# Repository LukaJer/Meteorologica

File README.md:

# Meteorologica

## A ultra-low-power, flexible Environment Monitioring Platform  

### Hardware Desctiption:  
- uC: STM32G071
- LoRa Module: RFM95
- power management: BQ25060 (4.4V - 10.2V input)
- I2C 
- 5 GPIOs: (PA0 (int0), PA8, PA15, PB3, PB5)
- JST ZH 1.5mm connectors
- 1.27mm header for for programming and debugging (SWD+UART)
#### Detailed Description  
It's centered around a STM32G071 microcontroller and uses LoRa for efficient and longish range communication. Currently it sends to a custom Gateway which forwards the data to a MQTT server but the code can be easily adapted to use another LoRa infrastructure like The Things Network. The LoRa Module is a RFM95.  
A 18650 cell (other Li Ion batterys can be used too) is used for power  which can be charged from a powersource (4.4V - 10.2V) or via USB-C. The charging is done by a TI BQ25060 which offers semi-MPPT functionality. The uC can read the solar and battery voltage.  
There are 5 GPIOs available (PA0 (int0), PA8, PA15, PB3, PB5) and a I2C bus. All GPIOs have footprints for pull-up/-down resistors or capacitors and 3V3 and GND connections next to them. JST ZH 1.5mm connectors are used and a 1.27mm header is present for programming and debugging (SWD+UART). Each sensor can be either powered directly from 3V3 or a toggleable 3V3 bus . NOTE: the toggleable bus is implemented in Hardware but untested and has currently software support.

### Software Description:
The project is written in Arduino.  
Each Station has it's own name so multiple can be used on a single Gateway. 
The station wakes up in specified Intervalls (2min) and checks if any of the sensor values have changed, if so it sends the data as a JSON to the Gatway. The data is send every 10th wakeup no matter the values as a heartbeat. 
Currently
- Bosch BME280
- Sensiron SHT31
- Lacrosse TX23
- MaXIM DS18B20
- generic simple rain sensor
are implemented an can be enabled by uncommenting code.

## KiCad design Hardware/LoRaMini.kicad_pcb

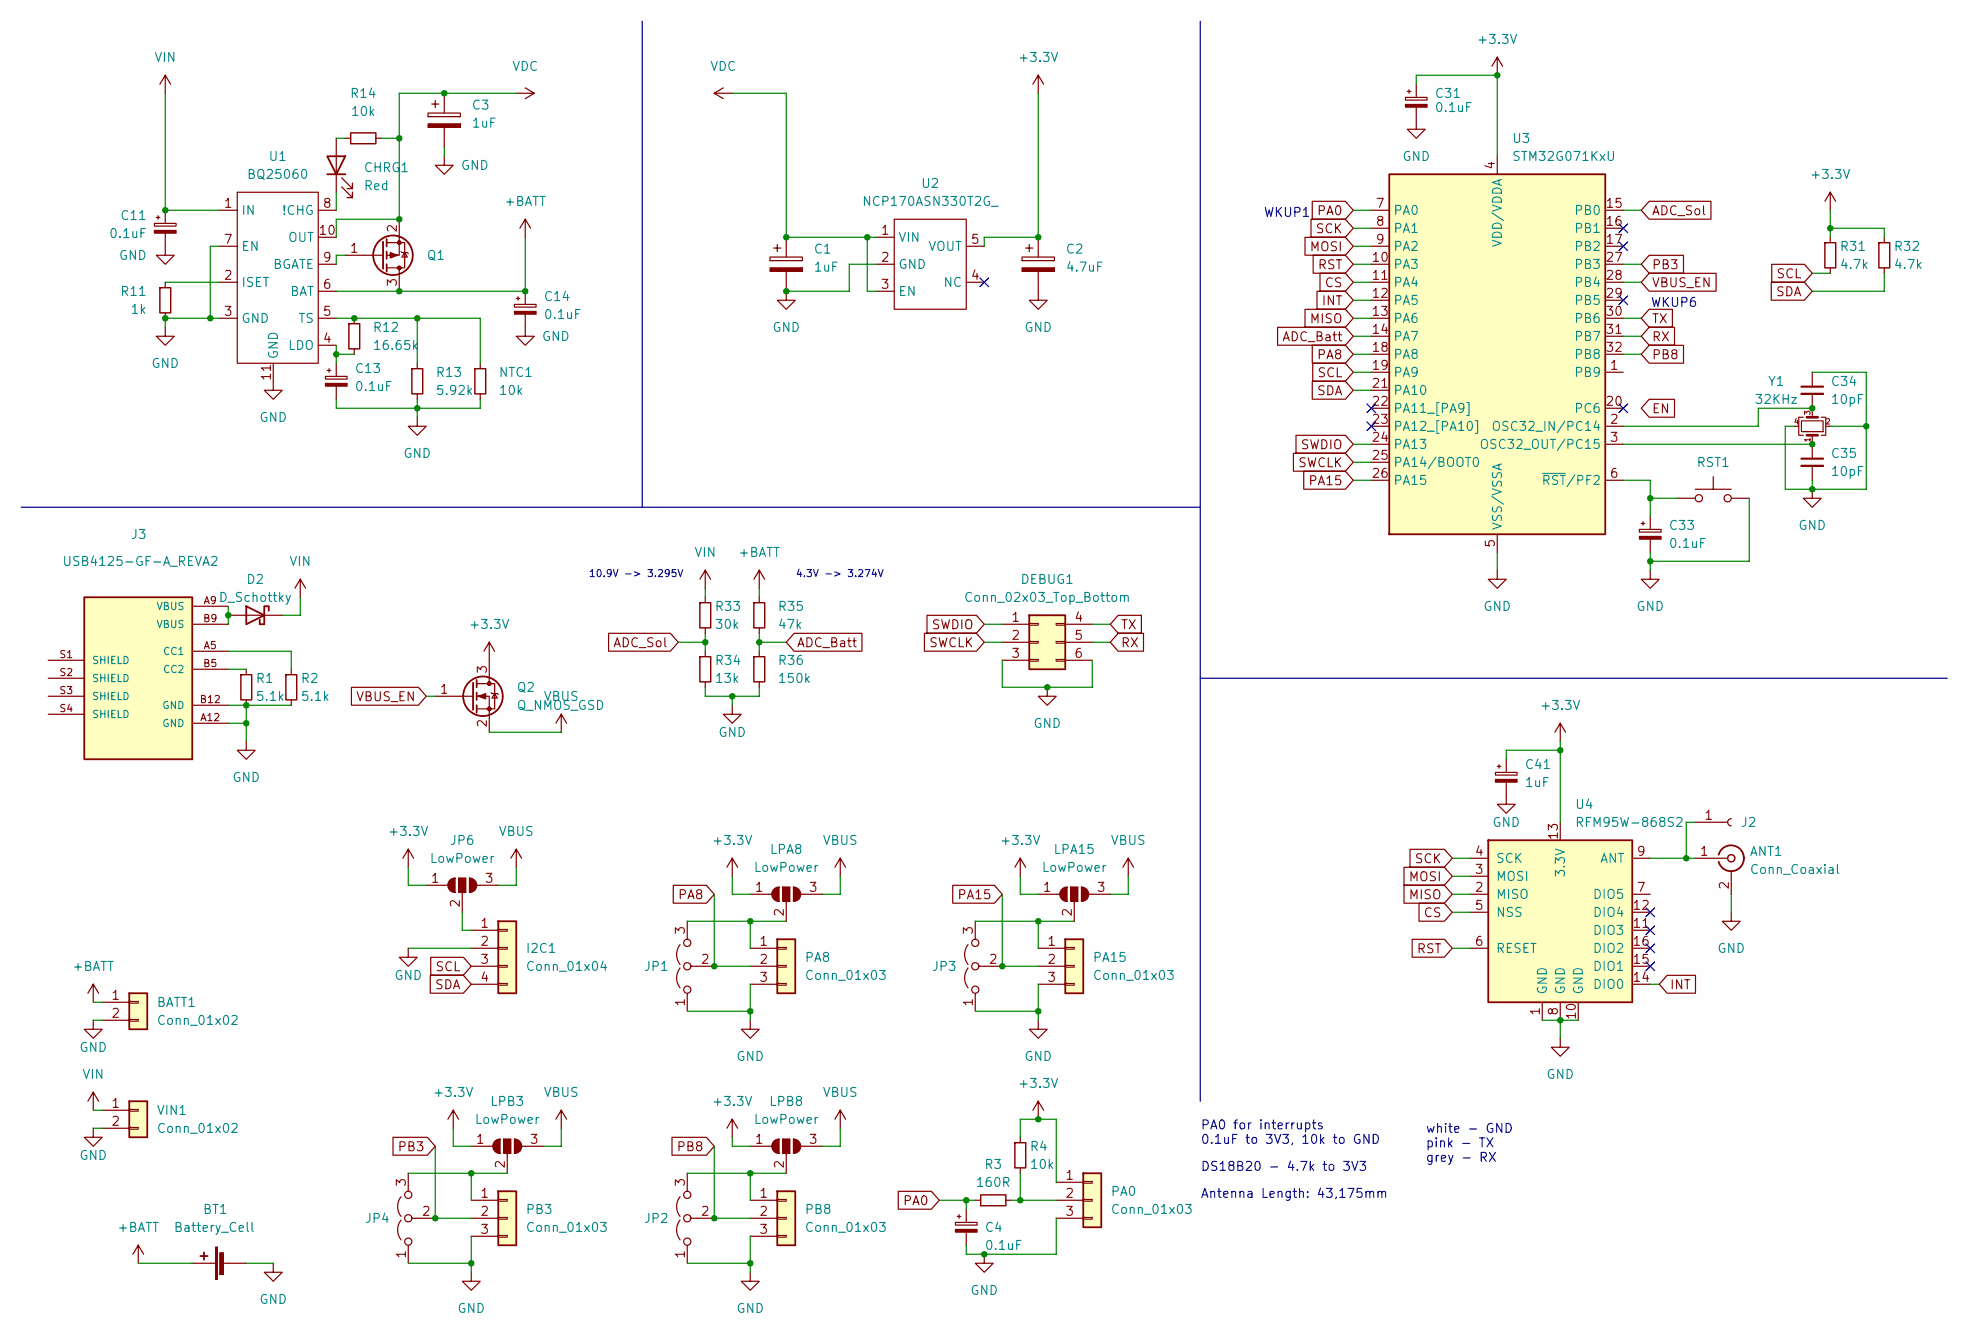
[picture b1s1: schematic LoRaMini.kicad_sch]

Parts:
ANT1: Conn_Coaxial; U.FL_Hirose_U.FL-R-SMT-1_Vertical
BATT1: Conn_01x02; JST_S2B-ZR-SM4A-TF(LF)(SN)
BT1: Battery_Cell; BatteryHolder_1x18650
C1, C3, C41: 1uF; C_1206_3216Metric
C2: 4.7uF; C_1206_3216Metric
C4, C13, C31, C33: 0.1uF; C_0805_2012Metric
C11, C14: 0.1uF; C_1206_3216Metric
C34, C35: 10pF; C_0805_2012Metric
CHRG1: Red; LED_1206_3216Metric
D2: D_Schottky; Nexperia_CFP3_SOD-123W
DEBUG1: Conn_02x03_Top_Bottom; PinHeader_2x03_P1.27mm_Vertical_SMD_My
I2C1: Conn_01x04; JST_S4B-ZR-SM4A-TF(LF)(SN)
J2: Conn_01x01_Female; Pin_D1.0mm_L10.0mm
J3: USB4125-GF-A_REVA2; GCT_USB4125-GF-A_REVA2; PARTREV Rev A2
JP1, JP2, JP3, JP4: Jumper_3_Open; Jumper_3_0805
JP6: LowPower; SolderJumper-3_P1.3mm_Open_Pad1.0x1.5mm
LPA8, LPA15: LowPower; SolderJumper-3_P1.3mm_Open_Pad1.0x1.5mm
LPB3, LPB8: LowPower; SolderJumper-3_P1.3mm_Open_Pad1.0x1.5mm
NTC1: 10k; R_0805_2012Metric
PA0, PA8, PA15: Conn_01x03; JST_S3B-ZR-SM4A-TF
PB3, PB8: Conn_01x03; JST_S3B-ZR-SM4A-TF
Q1: Q_PMOS_GSD; SOT-23
Q2: Q_NMOS_GSD; SOT-23
R1, R2: 5.1k; R_0805_2012Metric
R3: 160R; R_0805_2012Metric
R4, R14: 10k; R_0805_2012Metric
R11: 1k; R_0805_2012Metric
R12: 16.65k; R_0805_2012Metric
R13: 5.92k; R_0805_2012Metric
R31, R32: 4.7k; R_0805_2012Metric
R33: 30k; R_0805_2012Metric
R34: 13k; R_0805_2012Metric
R35: 47k; R_0805_2012Metric
R36: 150k; R_0805_2012Metric
RST1: SW_Push; SW_Push_SPST_NO_Alps_SKRK
U1: BQ25060; WSON-10-1EP_2x3mm_P0.5mm_EP0.84x2.4mm
U2: NCP170ASN330T2G_; TSOP-5_1.65x3.05mm_P0.95mm
U3: STM32G071KxU; UFQFPN-32-1EP_5x5mm_P0.5mm_EP3.5x3.5mm
U4: RFM95W-868S2; HOPERF_RFM9XW_SMD
VIN1: Conn_01x02; JST_S2B-ZR-SM4A-TF(LF)(SN)
Y1: 32KHz; Crystal_SMD_2520-4Pin_2.5x2.0mm

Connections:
+3V3: C2.1, C31.1, C41.1, JP6.1 (A), LPA8.1 (A), LPA15.1 (A), LPB3.1 (A), LPB8.1 (A), PA0.1, Q2.3 (D), R4.1, R31.1, R32.1, U2.5 (VOUT), U3.4 (VDD/VDDA), U4.13 (3.3V)
+BATT: BATT1.1, BT1.1 (+), C14.1, Q1.3 (D), R35.1, U1.6 (BAT); also elsewhere on the board
ADC_Batt: R35.2, R36.1, U3.14 (PA7)
ADC_Sol: R33.2, R34.1, U3.15 (PB0)
CS: U3.11 (PA4), U4.5 (NSS)
GND: ANT1.2 (Ext), BATT1.2, BT1.2 (-), C1.2, C2.2, C3.2, C4.2, C11.2, C13.2, C14.2, C31.2, C33.2, C34.1, C35.2, C41.2, DEBUG1.3, DEBUG1.6, I2C1.2, J3.A12 (GND), J3.B12 (GND), JP1.1 (A), JP2.1 (A), JP3.1 (A), JP4.1 (A), NTC1.2, PA0.3, PA8.3, PA15.3, PB3.3, PB8.3, R1.2, R2.2, R11.2, R13.2, R34.2, R36.2, RST1.2, U1.3 (GND), U1.7 (EN), U1.11 (GND), U2.2 (GND), U3.5 (VSS/VSSA), U3.33 (VSS/VSSA), U4.1 (GND), U4.8 (GND), U4.10 (GND), VIN1.2, Y1.2, Y1.4; also elsewhere on the board
INT: U3.12 (PA5), U4.14 (DIO0)
MISO: U3.13 (PA6), U4.2 (MISO)
MOSI: U3.9 (PA2), U4.3 (MOSI)
unnamed 9: ANT1.1 (In), J2.1, U4.9 (ANT); also elsewhere on the board
unnamed: C13.1, R12.2, U1.4 (LDO)
unnamed 11: C33.1, RST1.1, U3.6 (~RST/PF2); also elsewhere on the board
unnamed: C34.2, U3.2 (OSC32_IN/PC14), Y1.3
unnamed: C35.1, U3.3 (OSC32_OUT/PC15), Y1.1
unnamed: CHRG1.1 (K), U1.8 (!CHG)
unnamed: CHRG1.2 (A), R14.1
unnamed: D2.2 (A), J3.A9 (VBUS), J3.B9 (VBUS)
unnamed 17: I2C1.1, JP6.2 (C); also elsewhere on the board
unnamed: J3.A5 (CC1), R2.1
unnamed: J3.B5 (CC2), R1.1
unnamed: JP1.3 (B), LPA8.2 (C), PA8.1
unnamed: JP2.3 (B), LPB8.2 (C), PB8.1
unnamed: JP3.3 (B), LPA15.2 (C), PA15.1
unnamed: JP4.3 (B), LPB3.2 (C), PB3.1
unnamed: NTC1.1, R12.1, R13.1, U1.5 (TS)
unnamed: PA0.2, R3.2, R4.2
unnamed: Q1.1 (G), U1.9 (BGATE)
unnamed: R11.1, U1.2 (ISET)
PA0: C4.1, R3.1, U3.7 (PA0)
PA8: JP1.2 (C), PA8.2, U3.18 (PA8)
PA15: JP3.2 (C), PA15.2, U3.26 (PA15)
PB3: JP4.2 (C), PB3.2, U3.27 (PB3)
PB8: JP2.2 (C), PB8.2, U3.32 (PB8)
RST: U3.10 (PA3), U4.6 (RESET)
RX: DEBUG1.5, U3.31 (PB7)
SCK: U3.8 (PA1), U4.4 (SCK)
SCL: I2C1.3, R31.2, U3.19 (PA9); also elsewhere on the board
SDA: I2C1.4, R32.2, U3.21 (PA10); also elsewhere on the board
SWCLK: DEBUG1.2, U3.25 (PA14/BOOT0)
SWDIO: DEBUG1.1, U3.24 (PA13)
TX: DEBUG1.4, U3.30 (PB6)
VBUS: JP6.3 (B), LPA8.3 (B), LPA15.3 (B), LPB3.3 (B), LPB8.3 (B), Q2.2 (S)
VBUS_EN: Q2.1 (G), U3.28 (PB4)
VDC: C1.1, C3.1, Q1.2 (S), R14.2, U1.10 (OUT), U2.1 (VIN), U2.3 (EN)
VDD: C11.1, D2.1 (K), R33.1, U1.1 (IN), VIN1.1; also elsewhere on the board

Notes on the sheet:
DS18B20 - 4.7k to 3V3
4.3V -> 3.274V
Antenna Length: 43,175mm
PA0 for interrupts 0.1uF to 3V3, 10k to GND
10.9V -> 3.295V
white - GND pink - TX grey - RX
WKUP6
WKUP1

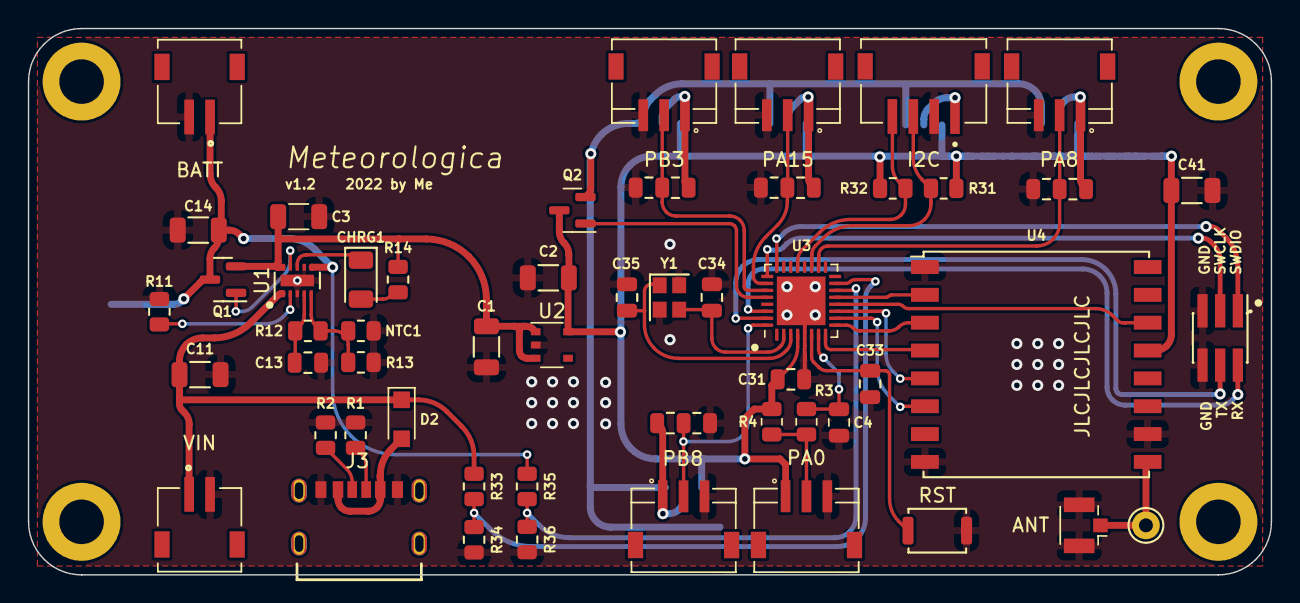
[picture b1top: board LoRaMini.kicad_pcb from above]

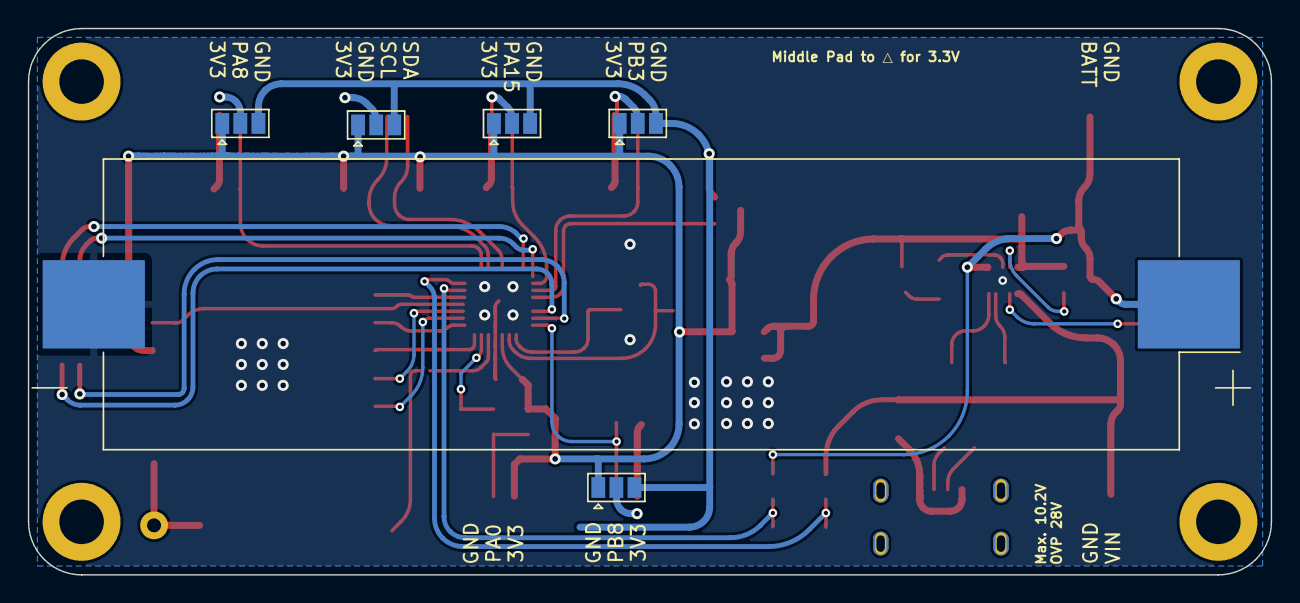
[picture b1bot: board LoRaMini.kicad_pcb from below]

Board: 2 copper layers, 89.3 x 39.2 mm, 59 parts (6 on the bottom side), 45 nets.

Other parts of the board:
ANT: Conn_Coaxial; U.FL_Hirose_U.FL-R-SMT-1_Vertical
BATT: Conn_01x02; JST_S2B-ZR-SM4A-TF(LF)(SN)
I2C: Conn_01x04; JST_S4B-ZR-SM4A-TF(LF)(SN)
RST: SW_Push; SW_Push_SPST_NO_Alps_SKRK
VIN: Conn_01x02; JST_S2B-ZR-SM4A-TF(LF)(SN)

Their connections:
+BATT: BATT.1; also elsewhere on the board
GND: ANT.2 (Ext), BATT.2, I2C.2, RST.2, VIN.2; also elsewhere on the board
unnamed 9: ANT.1 (In); also elsewhere on the board
unnamed 11: RST.1; also elsewhere on the board
unnamed 17: I2C.1; also elsewhere on the board
SCL: I2C.3; also elsewhere on the board
SDA: I2C.4; also elsewhere on the board
VDD: VIN.1; also elsewhere on the board

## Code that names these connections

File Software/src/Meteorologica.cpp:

#include <RH_RF95.h>
#include <Arduino.h>
#include <RHEncryptedDriver.h>
#include <Speck.h>
#include <Wire.h>
#include <ArduinoJson.h>
#include <LaCrosse_TX23.h>
#include "STM32LowPower.h"

// General Pin Definitions
#define RFM95_RST PA3
#define RFM95_CS PA4
#define RFM95_INT PA5
#define MISO PA6
#define MOSI PA2
#define SCK PA1
#define I2C_SDA PA10
#define I2C_SCL PA9

#define F_CPU 16000000

// Uncomment used Sensors:
//#define WIND
//#define BME280
//#define RMTSENS
//#define SHT31
#define RAIN

// Radiohead RF95 Driver
RH_RF95 rf95(RFM95_CS, RFM95_INT);			// Instanciate a LoRa driver
Speck myCipher;								// Instanciate a Speck block ciphering
RHEncryptedDriver myDriver(rf95, myCipher); // Instantiate the driver with those two

// Bosch BME280 Definition
#ifdef BME280
#include <Adafruit_Sensor.h>
#include <Adafruit_BME280.h>
#define SEALEVELPRESSURE_HPA (1013.25)
Adafruit_BME280 bme;
float Temp, Hum, Press;

#endif // BME280

// Sensorion SHT31 Definition
#ifdef SHT31
#include "Adafruit_SHT31.h"
Adafruit_SHT31 sht31 = Adafruit_SHT31();
float Temp1, Hum1;
#endif // SHT31

// MaXIM DS18B20 Definition
#ifdef RMTSENS
#define RemoteTempPin PA15
#include <OneWire.h>
#include <DallasTemperature.h>
OneWire oneWire(RemoteTempPin);
DallasTemperature RemoteSensor(&oneWire);
#endif // RMTSENS

// LaCrosse TX23 Definition
#ifdef WIND
#define Wind_Pin PB8
LaCrosse_TX23 anemometer = LaCrosse_TX23(Wind_Pin);
float speed, speed_old;
int dir, dir_old;
#endif // WIND

// Generic Rain Interrupt Sensor Definition
#ifdef RAIN
#define rainPin PA0 // fixed!!
volatile uint8_t rainPulses = 0;
void rainfct();
#endif // RAIN

float frequency = 868.0;																// LoRa Frequency
unsigned char encryptkey[16] = {1, 2, 3, 4, 5, 6, 7, 8, 9, 10, 11, 12, 13, 14, 15, 16}; // The very secret key
String name = "WSDev";																	// Name of the Weather Station
uint8_t HWMessageLen, nrWakeup = 0;
DynamicJsonDocument payload(512);			  // JSON Definition (might be shortened)
int SendInterval_LP = 600, SendInterval = 120; //  (Low Power) Send Intervall in Seconds
int ValChng = 0;							  // Tracks if values have changed
float VBatt, VSol;

void setup()
{
	// Set UART Pins
	Serial.setRx(PB7);
	Serial.setTx(PB6);
	Serial.begin(9600);

	payload["Name"] = name;
	Serial.println("WeatherLoRa Client: " + name);
	delay(100);

	// Set I2C Pins
	Wire.setSDA(I2C_SDA);
	Wire.setSCL(I2C_SCL);
	Wire.begin();

// Sensor Initalisation
#ifdef BME280
	unsigned status;
	status = bme.begin(0x76);
	if (!status)
	{
		Serial.println("Could not find a valid BME280 sensor, check wiring, address, sensor ID!");
		Serial.print("SensorID was: 0x");
		Serial.println(bme.sensorID(), 16);
		Serial.print("        ID of 0xFF probably means a bad address, a BMP 180 or BMP 085\n");
		Serial.print("   ID of 0x56-0x58 represents a BMP 280,\n");
		Serial.print("        ID of 0x60 represents a BME 280.\n");
		Serial.print("        ID of 0x61 represents a BME 680.\n");
		while (1)
			delay(10);
	}
#endif // BME280

#ifdef SHT31
	if (!sht31.begin(0x44))
	{ // Set to 0x45 for alternate i2c addr
		Serial.println("Couldn't find SHT31");
		while (1)
			delay(1);
	}
#endif // SHT31

#ifdef RMTSENS
	RemoteSensor.begin();
#endif // RMTSENS

	// Set SPI Pins
	SPI.setMISO(MISO);
	SPI.setMOSI(MOSI);
	SPI.setSCLK(SCK);
	delay(10);

	// LoRa Initalisation
	if (!rf95.init())
	{
		Serial.println("LoRa init failed");
		while (1) // Halt Startup if RF95 not found
			delay(1);
	}
	rf95.setFrequency(frequency);
	rf95.setTxPower(13);
	myCipher.setKey(encryptkey, sizeof(encryptkey));

	LowPower.begin();
// Enable Rain Interrupt
#ifdef RAIN
	pinMode(rainPin, INPUT_FLOATING);
	LowPower.attachInterruptWakeup(rainPin, rainfct, RISING, DEEP_SLEEP_MODE);
#endif // RAIN

	Serial.println("Setup completed");
	delay(1000);
}

void loop()
{

	float buffer = 0;

	delay(50);
	Serial.print("Wake-Up Nr: ");
	Serial.println(nrWakeup);
	// Keeping Track of #Wakeups
	nrWakeup++;
	// Data gets send every 10th wake-up independent wether data has changed: Heartbeat
	if (!(nrWakeup % 10))
	{
		ValChng = 1;
	}
	delay(50);
	Serial.print("Rainpulse: ");
	Serial.println(rainPulses);
// Read Wind Data
#ifdef WIND
	if (anemometer.read(speed, dir))
	{
		Serial.println("Wind found");
		/* Wind Data gets only sent if speed is greater 0 and
		Speedchange > 0.5 or
		ValChng = 1 or
		Direction Change > 0.5
		*/
		if (abs(speed_old - speed) > 0.5 || ValChng || ((abs(dir_old - dir) > 0.5) && speed > 0))
		{
			ValChng = 1;
			payload["Speed"] = speed;
			speed_old = speed;
			payload["Dir"] = dir * 22.5;
			dir_old = dir;
		}
	}
#endif // WIND

// Read BME280 Data
#ifdef BME280
	bme.takeForcedMeasurement();
	/* BEM280 Data gets only sent if
	Temperaturechange > 0.5°C or
	Humiditychange > 5%
	*/
	buffer = bme.readTemperature() / 1.0;
	if (abs(Temp - buffer) > 0.5 || ValChng)
	{
		ValChng = 1;
		payload["Temp"] = buffer;
		Temp = buffer;
	}
	buffer = roundf(bme.readHumidity() * 100) / 100;
	if (abs(Hum - buffer) > 5 || ValChng)
	{
		ValChng = 1;
		payload["Hum"] = buffer;
		Hum = buffer;
	}

	buffer = roundf(bme.readPressure()) / 100;
	if (abs(Press - buffer) > 0.5 || ValChng)
	{
		ValChng = 1;
		payload["Press"] = buffer;
		Press = buffer;
	}
#endif // BME280

// Read SHT 31 Data
#ifdef SHT31
	/* SHT31 Data gets only sent if
	Temperaturechange > 0.5°C or
	Humiditychange > 5%
	*/
	buffer = sht31.readTemperature();
	if (abs(Temp1 - buffer) > 0.5 || ValChng)
	{
		ValChng = 1;
		payload["Temp1"] = buffer;
		Temp1 = buffer;
	}

	buffer = sht31.readHumidity();
	if (abs(Hum1 - buffer) > 5 || ValChng)
	{
		ValChng = 1;
		payload["Hum1"] = buffer;
		Hum1 = buffer;
	}
#endif // SHT31

// Read Remote Sensor Data
#ifdef RMTSENS
	float RemoteTemp(NAN);
	RemoteSensor.requestTemperatures();
	RemoteTemp = RemoteSensor.getTempCByIndex(0);
	if (RemoteTemp != -127)
	{
		payload["RmtTmp"] = RemoteTemp;
	}
#endif // RMTSENS

#ifdef RAIN
	payload["RainC"] = rainPulses;
#endif // RAIN

	if (!ValChng)
	{
		// Don't send anything if no new Data or not a 10th wakeup
		Serial.println("No new Data, back to zzzz");
		delay(50);

		LowPower.deepSleep(SendInterval * 1000);
	}
	else
	{
		rainPulses = 0; // Reset RainPulses

		// Read Battery and Solar Voltages (8bit)
		VBatt = analogRead(PA7) * 4.3 / 1024;
		VSol = analogRead(PB0) * 10.9 / 1024;
		payload["VBatt"] = trunc(VBatt * 100) / 100;
		if (floor(VSol) > 0)
		{
			payload["VSol"] = trunc(VSol * 100) / 100;
		}

		size_t len = 32;
		char message[256]; // SerializedJSON, replace with len?
		len = payload.memoryUsage();
		Serial.println(len);
		serializeJson(payload, message); // Create String (Char Array) from JSON
		uint8_t data[len + 1]; // RFM95 input

		for (uint8_t i = 0; i <= len; i++) // Copy and Typecast Data from JSONString to uint8_t Array
		{
			data[i] = (uint8_t)message[i];
		}
		data[len + 1] = '\0';
		myDriver.send(data, sizeof(data)); // Send out ID + Sensor data to LoRa gateway
		Serial.print("Sent: ");
		delay(50);
		Serial.println((char *)&data);
		delay(50);
		rf95.sleep(); // Put RF95 to sleep
		ValChng = 0;
		delay(100);
		// Check if Battery is above 3V, if not use LowPower Intervall for Wakups, current not used!
		if (VBatt > 3.0)
			LowPower.deepSleep(SendInterval * 1000);
		else
		{
			LowPower.deepSleep(SendInterval_LP * 1000);
			ValChng = 1;
		}
	}
}


/* 
Rain Interrupt triggers this function
Increment Number of Rain Pulses an go back to Sleep
*/
#ifdef RAIN
void rainfct()
{
	rainPulses++;
	delay(50);
	LowPower.deepSleep();
}
#endif // RAIN

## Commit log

2022-09-28 SW init
2022-09-28 HW init
2022-09-28 updated gitignore
2022-10-19 fixed PA0
2022-10-19 added img
